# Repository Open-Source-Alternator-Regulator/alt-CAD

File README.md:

# CAD
Hardware design files for Alternator Regulator

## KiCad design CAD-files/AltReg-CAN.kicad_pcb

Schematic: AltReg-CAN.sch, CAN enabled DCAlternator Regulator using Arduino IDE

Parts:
C1: 4.7nF; SM0603_Capa; Part # 710-885012207070
C2, C5, C9, C10, C12, C13, C16, C17, C19, C20, C22, C25, C26, C27, C28: 100nF; SM0805; Part # 80-C0805C104K5R
C4, C11, C29: 150pF; SM0805; Part # 581-08055C151K
C6, C7: 47pF; SM0603_Capa; Part # 77-VJ0603A470JXACBC
C14: 0.47uF; SM0805; Part # Optional: 603-CC805KKX7R8BB474
C15, C18, C24: 4.7uF; SM1206; Part # 81-GRM31CR71E475KA88
C21, C23, C30: 0.47uF; SM0805; Part # 603-CC805KKX7R8BB474
C31: 47uF/100v; CP_10x16mm; Part # 647-UPW2A470MPD
C32: 56uF; CP_6.3x11mm; Part # 647-UHD1V560MED
D1: SMAJ64A; do214ac; Part # 24V Option: 511-SMAJ30A-TR
D2, D18: SMAJ64A; do214ac; Part # 625-SMAJ64A-E3
D3, D4: CG0603MLC-05E; SM0603; Part # 652-CG0603MLC-05E
D5: SMAJ30A; do214ac; Part # 511-SMAJ30A-TR
D6, D9, D13, D15, D16: ESD5Z5.0T1G; sod523; Mouser 863-ESD5Z5.0T1G
D7, D11: BAT54S; SOT23; Part # 863-BAT54SLT1G
D8, D19: FSV20100V; TO277-DIODE; Part # 512-FSV20100V
D12, D14, D17: S110; sod123HE; Part # 512-S110FP
D20: SSA210; DO-214AC(SMA); Part # 625-VSSA210-E3/61T
D21: NUP2105L; SOT23; Part # 863-NUP2105LT1G
D22: LED; LED-5MM-DUAL; Mouser 604-WP59EGW
H1, H2, H3, H4: HOLE; hole_3mm
J1: VBat-Shunt; Solder_trace
J2: I2C; PIN_ARRAY_2X1
J3: USB_MICRO; conn_usb_B_micro_vertical_TH
J4: USB_MICRO; conn_usb_B_micro_vertical
J5, J7: RJ45; RJ45_8; Part # 538-42410-8504 or 649-54602-908LF
J6: TERM; PIN_ARRAY_2X1
J8, J9, J10: GND-Opt; Solder_trace
K1: B; JST-B2B-XH-A; Part # JST XH2.54 2P
K2: A; JST-B2B-XH-A; Part # JST XH2.54 2P
L1: 10uH; SM0805; Part # 810-MLZ2012N100L
L2: 680uH; INDUCTOR_LRS; Part # 580-12LRS684C or 580-12LRS105C
P1: USB; PIN_ARRAY_5x1
P2: CONN_4; mkds_1,5-4; Part # 651-1935187
P3: CONN_5; mkds_1,5-5
P4: ICSP; pin_array_3x2; Part # 649-67996-206HLF
P5: CAN; PCB_Terminal_3.81mm_3pin; Part # 158-P02EK381V3-E
P6: CONN_6; mkds_1,5-6; Part # 651-1935815
Q1: NZT605; sot223
Q2: T3904; SOT23; Part # 863-MMBT3904LT1G
Q3, Q4: TPW4R50ANH; DSOP-8; Part# 757-TPW4R50ANHL1Q
R1: 30K 0.1%; SM0805; Part # 603-RT0805BRD0730KL
R2, R9, R26, R29: 10; SM0603_Resistor; Part # 71-CRCW0603-10-E3
R3, R10: 0; SM0603_Resistor; Part # Optional: 660-RK73Z1JTTD
R4, R7, R31: 37.8K; SM0603_Resistor; Mouser 667-ERJ-3EKF3742V
R5: 20K 0.1%; SM0805; Part # 603-RT0805BRD0720KL
R6, R23, R43: 1M; SM0603_Resistor; Part # 667-ERJ-3EKF1004V
R8, R19, R22, R40, R42: 1K; SM0603_Resistor; Part # 667-ERJ-3EKF1001V
R11: 221; SM0603_Resistor; Part # 279-CPF0603B221RE1
R12, R13: 27; SM0603_Resistor; Part # 667-ERJ-3EKF27R0V
R14, R15: 4.99K; SM0603_Resistor; Part # 284-APC0603B4K99N
R16: 0; SM0603_Resistor; Part # 660-RK73Z1JTTD
R17, R20, R21, R24, R35, R36, R37, R38: 10K; SM0603_Resistor; Part # 667-ERJ-3EKF1002V
R18: 1K; SM0603_Resistor; Part # Optional: 667-ERJ-3EKF1001V
R27, R30, R32, R33, R34, R41: 100; SM0603_Resistor; Part # 667-ERJ-3EKF1000V
R28: 120; SM1210; Mouser 603-RC1210FR-07120RL
R39: 100K; SM0603_Resistor; Part # 667-ERJ-3EKF1003V
S1: SW_DIP-8; SWDIP8u; Part # 774-2108MS or 642-DPL08(right angle)
TH1: 10K NTC; SM0402; Part # 81-NCP15XH103F03RC
TP1: Vdd; PINTST
U2: INA282; SO8E; Part # 595-INA282AIDR
U3: INA226; MSOP10-0.5; Part 3 595-INA226AIDGSR
U4: FT230X-S; ssop-16; Mouser Part# 895-FT230XS-R
U5: NCV1124; so-8; Mouser 863-NCV1124DR2G
U6: ATMEGA64M1-Ax; TQFP32; Part # 556-ATMEGA64M1-15AZ
U7: MIC4604; SO8E; Mouser 998-MIC4604YM-TR
U8: MCP2562; SO8E
U9: MC78M05CDT; DPAK2; Part # 511-L78M05CDT-TR
U10: MAX5033D; SO8E; Mouser Part# 700-MAX5033DASA
V1, V2, V3, V4, V5, V6, V7, V8, V9, V10, V11, V12, V13, V14, V15, V16, V17, V18, V19, V20: VIA; 02mm_via
X1: 16Mhz; resonator_smd

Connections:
+5V: C9.1, C16.2, C20.2, C22.1, C24.2, C26.1, C28.2, D7.2, D11.2, D12.2 (K), L1.2, P4.2, R14.1, R20.1, R21.1, R24.1, R35.1, R36.1, R37.1, R38.1, U2.3 (Ref_2), U2.7 (Ref1), U3.6 (Vss), U5.8 (Vcc), U6.4 (VCC), U8.3 (Vdd), U8.5 (Vio), U9.3 (OUT)
/3.3v: C10.2, R17.1, U4.3 (VCCIO), U4.10 (3V3OUT), U4.11 (~RESET)
/A_NTC: R32.2, U6.13 ((PCINT21/ADC2/ACMP2)PD5)
/B: D8.1 (A), P6.3, Q3.2 (D), Q4.2 (D)
/B_NTC: R34.2, U6.14 ((PCINT22/ADC3/INT0/ACMPN2)PD6)
/C: C18.1, D19.2 (K), P6.4, Q3.3 (S), Q4.3 (S), U7.4 (HS)
/CAN-H: D21.1, J5.1, J6.2 (PM), J7.1, P5.1, U8.7 (CANH)
/CAN-L: D21.2, J5.2, J7.2, P5.3, R28.2, U8.6 (CANL)
/CAN_GND: J5.3, J5.7, J7.3, J7.7
/CAN_shield: C14.1, J5.6, J7.6, P5.2 (PM)
/DIP-1: S1.1, U6.26 ((PCINT5/ADC6/INT2/ACMPN1/AMP2-)PB5)
/DIP-2: S1.2, U6.28 ((PCINT7/ADC4/SCK/PSCOUT0B)PB7)
/DIP-3: S1.3, U6.29 ((PCINT16/PSCOUT0A)PD0)
/DIP-4: S1.4, U6.18 ((PCINT13/ADC9/ACMP3/AMP1+)PC5)
/DIP-5: S1.5, U6.17 ((PCINT12/ADC8/ACMPN3/AMP1-)PC4)
/DIP-6: S1.6, U6.22 ((PCINT14/ADC10/ACMP1)PC6)
/DIP-7: S1.7, U6.16 ((PCINT2/ADC5/INT1/ACMPN0)PB2)
/DIP-8: S1.8, U6.15 ((PCINT23/ACMP0)PD7)
/FET_NTC: R24.2, TH1.2, U6.27 ((PCINT6/ADC7/PSCOUT1B)PB6)
/Feature_IN: R27.2, U6.24 ((PCINT4/AMP0+)PB4)
/Feature_OUT: R8.1, U6.23 ((PCINT3/AMP0-)PB3)
/Field PWM: U6.3 ((PCINT9/PSCIN1/OC1B/~SS_A~)PC1), U7.5 (HI)
/HO: R26.2, R29.2, U7.3 (HO)
/HO-Q1: Q4.1 (G), R26.1
/HO-Q3: Q3.1 (G), R29.1
/Hb: C18.2, D17.2 (K), U7.2 (Hb)
/LED_Green: D13.2 (K), P4.1, R42.1, U6.1 ((PCINT18/PSCIN2/OC1A/MISO_A)PD2)
/LED_Red: R40.1, U6.32 ((PCINT17/CLKO/PSCIN0)PD1)
/POL-PROT: C31.1, D14.2 (K), U10.5 (On/~Off), U10.7 (Vin)
/SCL: J2.2 (PM), R37.2, U3.5 (SCL), U6.9 ((PCINT1/MOSI/PSCOUT2B)PB1)
/SDA: J2.1, R35.2, U3.4 (SDA), U6.8 ((PCINT0/MISO/PSCOUT2A)PB0)
/Stator_IRQ: U5.7 (OUT1), U6.30 ((PCINT8/INT3/PSCOUT1A)PC0), U7.6 (LI)
/USB-SHLD: C1.2, J3.6, J4.6, P1.5, R6.2
/XD: C15.2, D12.1 (A), J3.1, J4.1, P1.1, U4.12 (VCC)
/XH: C27.2, C29.2, D20.2 (K), L2.1, U10.8 (LX)
/~RESET: C13.2, D7.3, P4.5, R20.2, U6.31 ((PCINT24/OCD/~RESET~)PE0)
Alt+: D8.2 (K), P6.1, P6.2
Alt-: D19.1 (A), J8.2, J9.2, J10.2, P6.5, P6.6
BAT-: C1.1, C4.1, C5.2, C6.1, C7.1, C9.2, C10.1, C11.2, C12.2, C15.1, C16.1, C17.1, C19.1, C20.1, C21.2, C22.2, C23.2, C24.1, C25.2, C26.2, C28.1, C30.2, C31.2, C32.2, D1.1 (A), D2.1 (A), D3.1 (A), D4.1 (A), D5.1 (A), D6.1 (A), D7.1, D9.1 (A), D11.1, D13.1 (A), D15.1 (A), D16.1 (A), D18.1 (A), D20.1 (A), D21.3, D22.K, J3.5, J4.5, J8.1, J9.1, J10.1, P1.4, P2.1, P4.6, Q1.3, R5.1, R6.1, R16.1, R18.2, R23.1, R30.2, R31.1, R33.2, R39.1, R41.2, S1.9, S1.10, S1.11, S1.12, S1.13, S1.14, S1.15, S1.16, TH1.1, U2.2 (GND), U3.1 (A1), U3.2 (A0), U3.7 (GND), U4.5 (GND), U4.6 (~CTS), U4.13 (GND), U5.4 (GND), U5.5 (DIAG), U6.5 (GND), U6.20 (AGND), U7.7 (Vss), U8.2 (Vss), U8.8 (STBY), U9.2 (GND), U10.3 (SGND), U10.6 (GND), V1.1, V2.1, V3.1, V4.1, V5.1, V6.1, V7.1, V8.1, V9.1, V10.1, V11.1, V12.1, V13.1, V14.1, V15.1, V16.1, V17.1, V18.1, V19.1, V20.1, X1.2
Current Shunt +: D2.2 (K), J1.1, P2.3, R2.1
Current Shunt -: D1.2 (K), P2.4, R9.1
Enable: D14.1 (A), D18.2 (K), P3.5
Feature-IN: P3.3, R4.1
Feature-OUT: P3.4, Q1.2
unnamed: K2.1, R30.1
unnamed: K1.1, R33.1
unnamed: D22.A1, R40.2
unnamed: D22.A2, R42.2
unnamed: R15.1, U2.5 (Out)
unnamed: C2.2, R2.2, R3.1, U2.8 (In+)
unnamed: C2.1, R9.2, R10.1, U2.1 (In-)
unnamed: R31.2, U5.1 (Radj)
unnamed: C11.1, R7.2, U5.2 (IN1)
unnamed: J5.8, J7.8
unnamed: U6.7 ((PCINT11/T1/ICP1B/RXCAN)PC3), U8.4 (RXD)
unnamed: U6.6 ((PCINT10/T0/TXCAN)PC2), U8.1 (TXD)
unnamed: C23.1, D15.2 (K), K2.2 (PM), R32.1, R36.2
unnamed: C12.1, D11.3, R4.2, R23.2, R27.1
unnamed: C4.2, D5.2 (K), R1.2, R5.2, U3.8 (Vbus)
unnamed: J5.4, J7.4
unnamed: C25.1, U10.2 (VD)
unnamed: C27.1, U10.1 (BST)
unnamed: J5.5, J7.5
unnamed: C29.1, R41.1
unnamed: R16.2, U6.25 ((PCINT15/D2A/AMP2+)PC7)
unnamed: R39.2, R43.1, U10.4 (FB)
unnamed: C17.2, U6.21 (AREF(ISRC))
unnamed: U6.11 ((PCINT26/ADC0/XTAL2)PE2), X1.1
unnamed: C21.1, D16.2 (K), K1.2 (PM), R34.1, R38.2
unnamed: J3.4, J4.4
unnamed: C7.2, D4.2 (K), J3.3, J4.3, P1.3, R13.1
unnamed: Q1.1, R8.2
unnamed: R19.2, U7.8 (LO)
unnamed: R10.2, R11.1, R14.2, U3.9 (Vin-)
unnamed: R3.2, R11.2, R15.2, U3.10 (Vin+)
unnamed: C14.2, R18.1
unnamed: J6.1, R28.1
unnamed: U6.10 ((PCINT25/OC0B/XTAL1)PE1), X1.3
unnamed: C6.2, D3.2 (K), J3.2, J4.2, P1.2, R12.1
unnamed: Q2.1 (B), R17.2
unnamed: R12.2, U4.9 (USBDM)
unnamed: R13.2, U4.8 (USBDP)
unnamed: Q2.2 (E), U4.2 (~RTS)
unnamed: R22.2, U4.1 (TXD)
unnamed: D9.2 (K), P4.3, R22.1, U6.12 ((PCINT20/ADC1/RXD/RXLIN/ICP1A/SCK_A)PD4)
unnamed: D6.2 (K), P4.4, U4.4 (RXD), U6.2 ((PCINT19/TXD/TXLIN/OC0A/~SS~/MOSI_A)PD3)
unnamed: C13.1, Q2.3 (C), R21.2
unnamed: C19.2, L1.1, U6.19 (AVCC)
STATOR: P3.1, R7.1
Tach-OUT: P3.2, R19.1
VBat+: J1.2, P2.2, R1.1
VDD: C5.1, C30.1, C32.1, D17.1 (A), L2.2, R43.2, TP1.1, U2.6 (V+), U7.1 (Vdd), U9.1 (IN)

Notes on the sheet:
D12 allows configuration of unit via USB on bench
Dip 1..2 = CAN battery ID Dip 3..5 = Charge profile / Battery type Dip 6..7 = Bat Capacity Dip 8 = Small Alt Mode
P8 may be used to optionaly connect directly to wires, or a bulkhead connector (e.g. NMEA-2000). Ref CANopen spec CiA-303
A-Temp
Vdd = 13.4v
High Drive: A-jumper-B, C -field- D Low Drive: A -field- B, C-jumper-D
Design Point: 65v max Battery / System Voltage (32v max with '24v' stuffing option)
Q1/Q3 temp sensor
Stuffing Option - on-board USB
B-Temp
Note: When using RJ-45 connectors, utilize "DMX Termination Plug" on end nodes
Option: Solder Jumpers to allow low wire count install See Users Manual.
Note: D20 & C32 are critical components. Take care with part # subs. See MAX5033D datasheet for details
Note: Configure uC to use external Vcc (5v) ADC Vref
Shield Gnd Populate R18, C14 only if needed
A-Temp: Alternator B-Temp: Battery, or optionaly 2nd alterantor (See users guide)
CAUTION: If J1 & J8..J10 are bridged on PCB, install a 2-position connector for P2. Leaving the BAT- and VBat+ pins unaccessable.
24v - stuffing option: Install R3, R10, R16 Do not populate R11, R14, R15, R5, C5, U2 Change C4 to .1uF, change R1 to 10-ohms Change D1, D2 to SMJ30A (511-SMAJ30A-TR) Sysem max becomes 30V (battery target 24v max) R16 is used to signal to software this otion is installed.

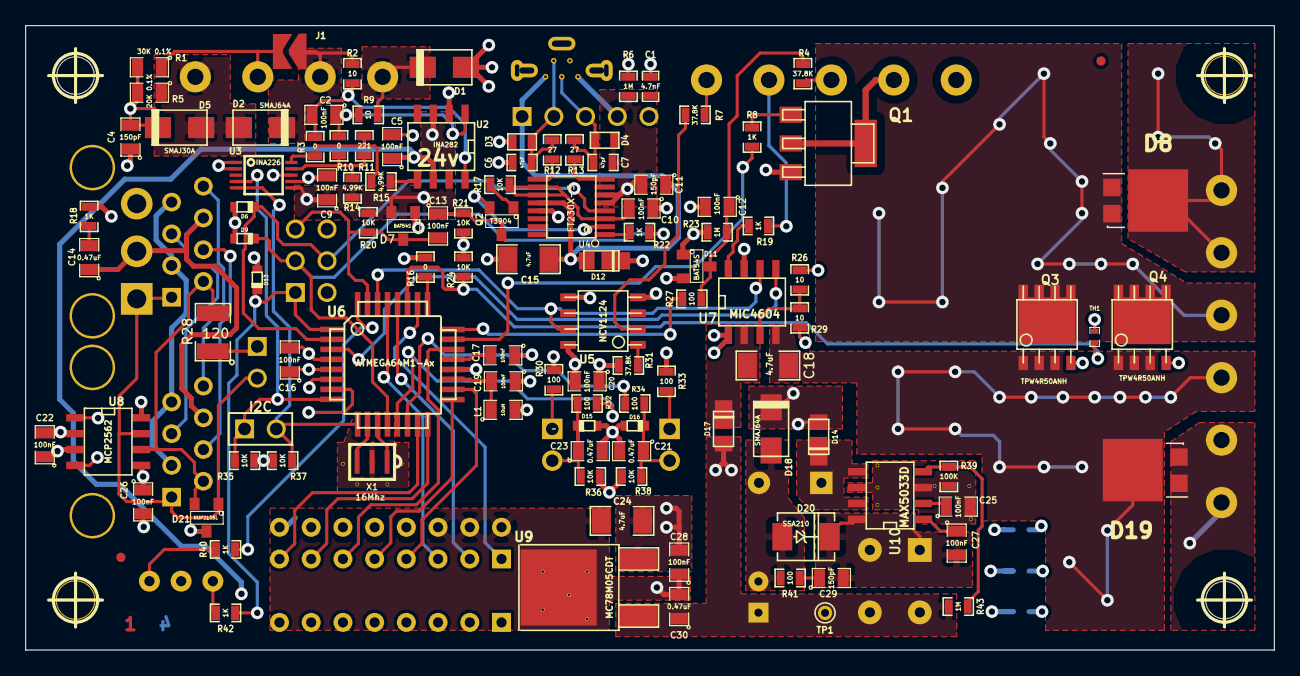
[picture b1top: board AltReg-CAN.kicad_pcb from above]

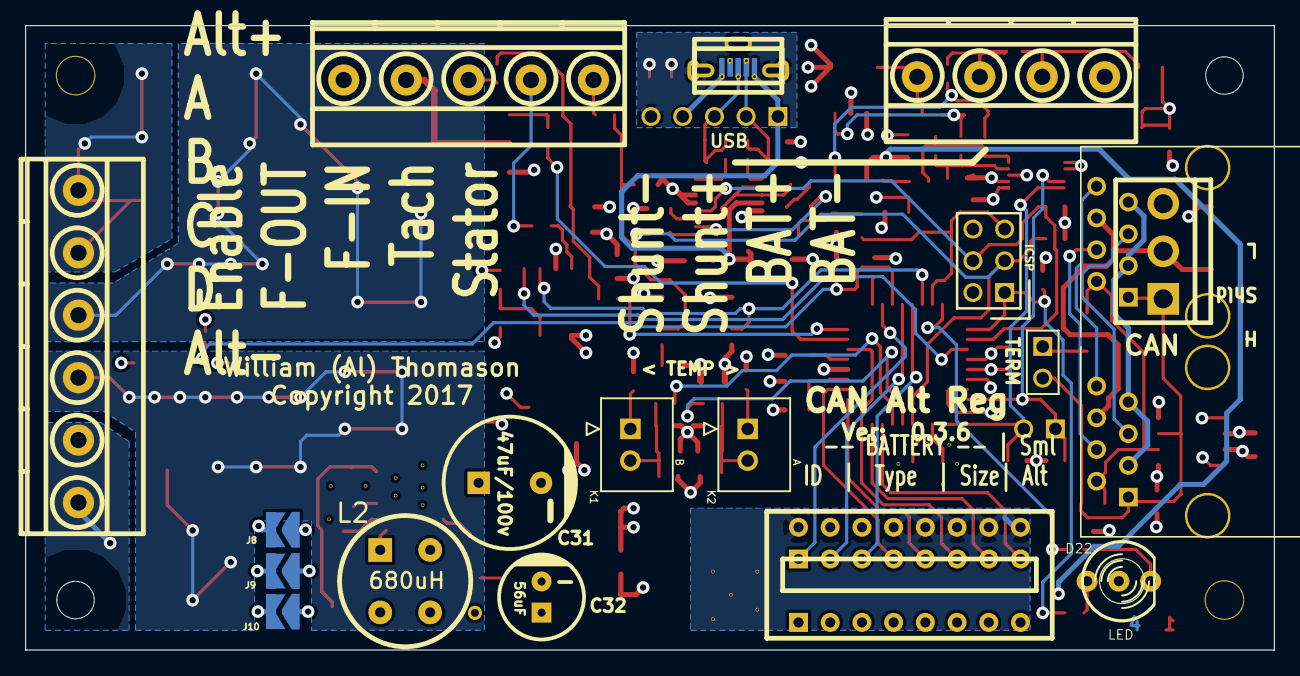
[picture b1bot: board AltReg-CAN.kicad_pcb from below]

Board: 4 copper layers, 100.0 x 50.0 mm, 156 parts (21 on the bottom side), 92 nets.

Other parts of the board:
fiducial_075_300_round, fiducial_075_300_round#2: VAL**; fiducial_075_300_round

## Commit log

2019-01-20 Create CAD-files

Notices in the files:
CAD-files/AltReg-CAN.kicad_pcb:
Copyright 2016 -  William A. Thomason
Licensed under a Creative Commons Attribution-ShareAlike 4.0 International License.
Copyright 2017
CAD-files/AltReg-CAN.sch:
Copyright 2017 -  William A. Thomason
